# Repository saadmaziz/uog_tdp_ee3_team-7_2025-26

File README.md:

# UoG_TDP-EE3_Team_7
Design Files for the 3rd year EEE team design project at the University of Glasgow. Line following rover, with obstacle avoidance, traffic lights detection, remote control using an ESP-32 connected to a laptop and a Logitech 3D Pro Joystick.
The  Centeral processor is a Freescale NXP Frdm KL25Z.

1 - Team Organisation and 6 - General Documents are not uploaded as they may contain non-relavant information that should not be made public

The team consisted of 5 members.

My personal contributions spanned all of the software, all of the mechanical design, a substantial part of the electronic hardware design, and most of the integration.

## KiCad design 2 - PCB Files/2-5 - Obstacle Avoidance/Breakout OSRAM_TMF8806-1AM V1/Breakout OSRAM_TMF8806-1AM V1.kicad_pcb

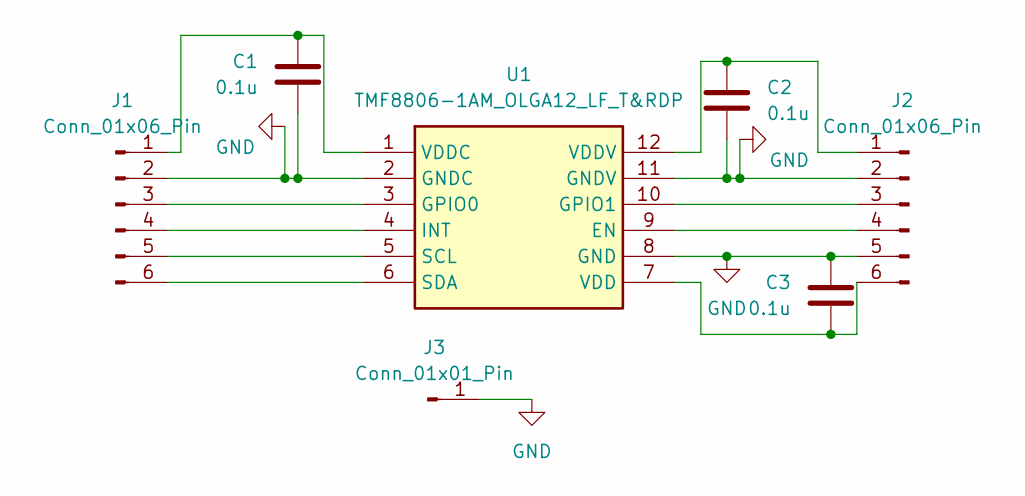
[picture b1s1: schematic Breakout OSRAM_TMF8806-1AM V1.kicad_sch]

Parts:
C1, C2, C3: 0.1u; C_0603_1608Metric
J1, J2: Conn_01x06_Pin; PinHeader_1x06_P2.54mm_Vertical
J3: Conn_01x01_Pin; PinHeader_1x01_P2.54mm_Vertical
U1: TMF8806-1AM_OLGA12_LF_T&RDP; TMF88061AMOLGA12LFTRDP; Manufacturer_Part_Number TMF8806-1AM OLGA12 LF T&RDP

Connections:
GND: C1.2, C2.2, C3.1, J1.2, J2.2, J2.5, J3.1, U1.2 (GNDC), U1.8 (GND), U1.11 (GNDV)
unnamed: C1.1, J1.1, U1.1 (VDDC)
unnamed: J1.3, U1.3 (GPIO0)
unnamed: J1.4, U1.4 (INT)
unnamed: J1.5, U1.5 (SCL)
unnamed: J1.6, U1.6 (SDA)
unnamed: C2.1, J2.1, U1.12 (VDDV)
unnamed: J2.3, U1.10 (GPIO1)
unnamed: J2.4, U1.9 (EN)
unnamed: C3.2, J2.6, U1.7 (VDD)

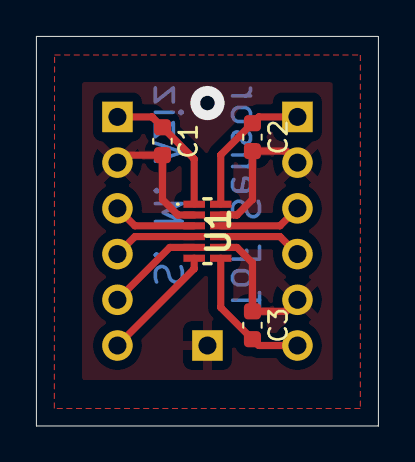
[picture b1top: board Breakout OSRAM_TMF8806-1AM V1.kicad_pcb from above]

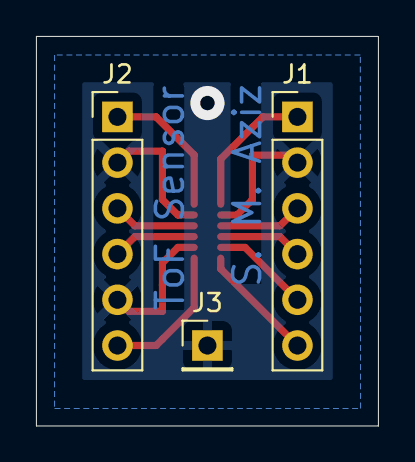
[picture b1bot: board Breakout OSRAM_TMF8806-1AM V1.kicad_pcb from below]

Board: 2 copper layers, 19.0 x 21.6 mm, 7 parts (3 on the bottom side), 10 nets.

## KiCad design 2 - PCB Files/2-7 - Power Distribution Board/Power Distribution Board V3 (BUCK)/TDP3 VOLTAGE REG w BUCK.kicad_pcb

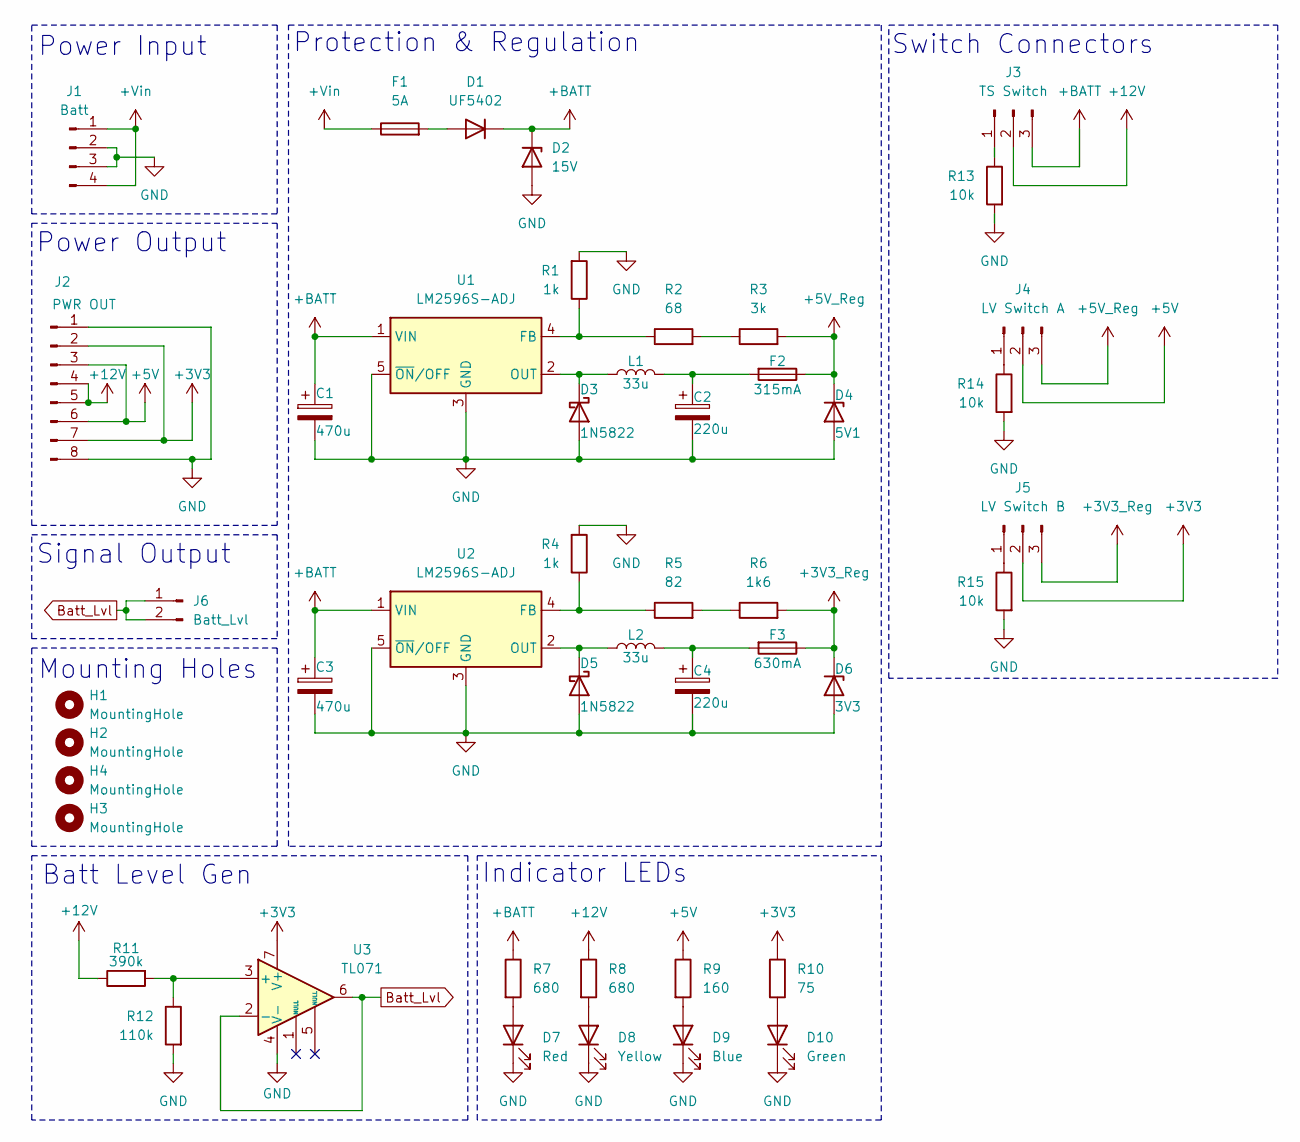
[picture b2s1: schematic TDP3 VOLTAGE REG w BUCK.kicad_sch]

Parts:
C1, C3: 470u; CP_Radial_D13.0mm_P5.00mm
C2, C4: 220u; CP_Radial_D10.0mm_P5.00mm
D1: UF5402; D_DO-201AD_P15.24mm_Horizontal
D2: 15V; D_DO-35_SOD27_P7.62mm_Horizontal
D3, D5: 1N5822; D_DO-201AD_P15.24mm_Horizontal
D4: 5V1; D_DO-35_SOD27_P7.62mm_Horizontal
D6: 3V3; D_DO-35_SOD27_P7.62mm_Horizontal
D7: Red; LED_0805_2012Metric_Pad1.15x1.40mm_HandSolder
D8: Yellow; LED_0805_2012Metric_Pad1.15x1.40mm_HandSolder
D9: Blue; LED_0805_2012Metric_Pad1.15x1.40mm_HandSolder
D10: Green; LED_0805_2012Metric_Pad1.15x1.40mm_HandSolder
F1: 5A; CamdenBoss CFH02_W Fuse Holder
F2: 315mA; CamdenBoss CFH02_W Fuse Holder
F3: 630mA; CamdenBoss CFH02_W Fuse Holder
H1, H2, H3, H4: MountingHole; MountingHole_3.2mm_M3
J1: Batt; Molex_KK-254_AE-6410-04A_1x04_P2.54mm_Vertical
J2: PWR OUT; PinHeader_1x08_P2.54mm_Vertical
J3: TS Switch; Molex_KK-254_AE-6410-03A_1x03_P2.54mm_Vertical
J4: LV Switch A; Molex_KK-254_AE-6410-03A_1x03_P2.54mm_Vertical
J5: LV Switch B; Molex_KK-254_AE-6410-03A_1x03_P2.54mm_Vertical
J6: Batt_Lvl; PinHeader_1x02_P2.54mm_Vertical
L1, L2: 33u; L_12x12mm_H6mm
R1, R4: 1k; R_0805_2012Metric_Pad1.20x1.40mm_HandSolder
R2: 68; R_0805_2012Metric_Pad1.20x1.40mm_HandSolder
R3: 3k; R_0805_2012Metric_Pad1.20x1.40mm_HandSolder
R5: 82; R_0805_2012Metric_Pad1.20x1.40mm_HandSolder
R6: 1k6; R_0805_2012Metric_Pad1.20x1.40mm_HandSolder
R7, R8: 680; R_0805_2012Metric_Pad1.20x1.40mm_HandSolder
R9: 160; R_0805_2012Metric_Pad1.20x1.40mm_HandSolder
R10: 75; R_0805_2012Metric_Pad1.20x1.40mm_HandSolder
R11: 390k; R_0805_2012Metric_Pad1.20x1.40mm_HandSolder
R12: 110k; R_0805_2012Metric_Pad1.20x1.40mm_HandSolder
R13, R14, R15: 10k; R_0805_2012Metric_Pad1.20x1.40mm_HandSolder
U1, U2: LM2596S-ADJ; TO-263-5_TabPin3
U3: TL071; DIP-8_W7.62mm_LongPads

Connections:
+3V3: J2.2, J2.7, J5.2, R10.1, U3.7 (V+)
+3V3_Reg: D6.1 (K), F3.1, J5.3, R6.2
+5V: J2.3, J2.6, J4.2, R9.1
+5V_Reg: D4.1 (K), F2.1, J4.3, R3.2
+12V: J2.4, J2.5, J3.2, R8.1, R11.1
+BATT: C1.1, C3.1, D1.1 (K), D2.1 (K), J3.3, R7.1, U1.1 (VIN), U2.1 (VIN)
+Vin: F1.1, J1.1, J1.4
Batt_Lvl: J6.1, J6.2, U3.2 (-), U3.6
GND: C1.2, C2.2, C3.2, C4.2, D2.2 (A), D3.2 (A), D4.2 (A), D5.2 (A), D6.2 (A), D7.1 (K), D8.1 (K), D9.1 (K), D10.1 (K), J1.2, J1.3, J2.1, J2.8, R1.2, R4.2, R12.2, R13.2, R14.2, R15.2, U1.3 (GND), U1.5 (~ON/OFF), U2.3 (GND), U2.5 (~ON/OFF), U3.4 (V-)
unnamed: C2.1, F2.2, L1.2
unnamed: C4.1, F3.2, L2.2
unnamed: D1.2 (A), F1.2
unnamed: D3.1 (K), L1.1, U1.2 (OUT)
unnamed: D5.1 (K), L2.1, U2.2 (OUT)
unnamed: D7.2 (A), R7.2
unnamed: D8.2 (A), R8.2
unnamed: D9.2 (A), R9.2
unnamed: D10.2 (A), R10.2
unnamed: J3.1, R13.1
unnamed: J4.1, R14.1
unnamed: J5.1, R15.1
unnamed: R2.2, R3.1
unnamed: R5.2, R6.1
unnamed: R1.1, R2.1, U1.4 (FB)
unnamed: R4.1, R5.1, U2.4 (FB)
unnamed: R11.2, R12.1, U3.3 (+)

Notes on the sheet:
Mounting Holes
Power Input
Indicator LEDs
Power Output
Signal Output
Switch Connectors
Batt Level Gen
Protection & Regulation

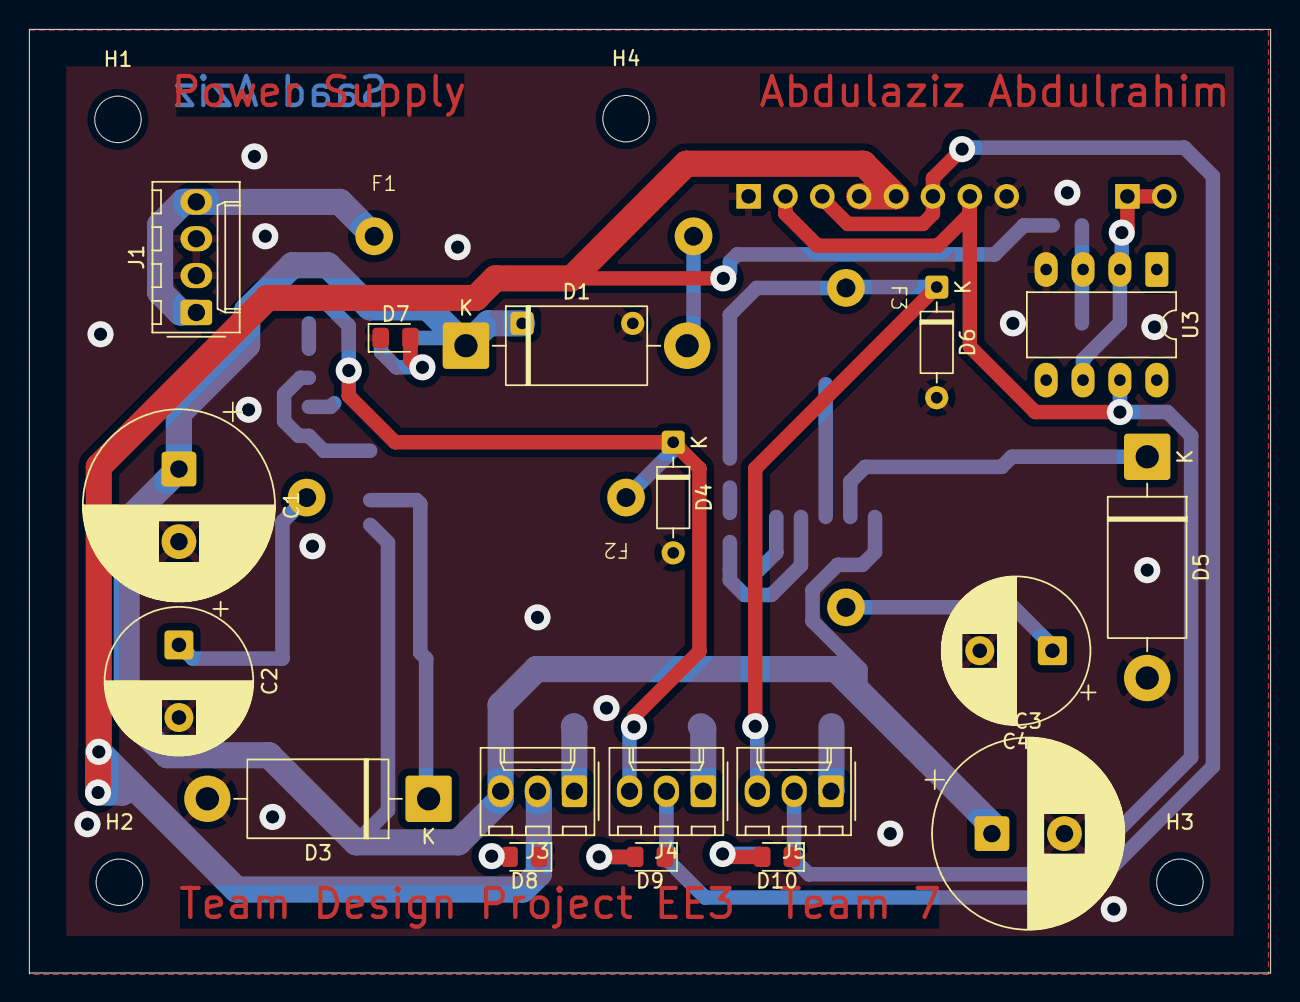
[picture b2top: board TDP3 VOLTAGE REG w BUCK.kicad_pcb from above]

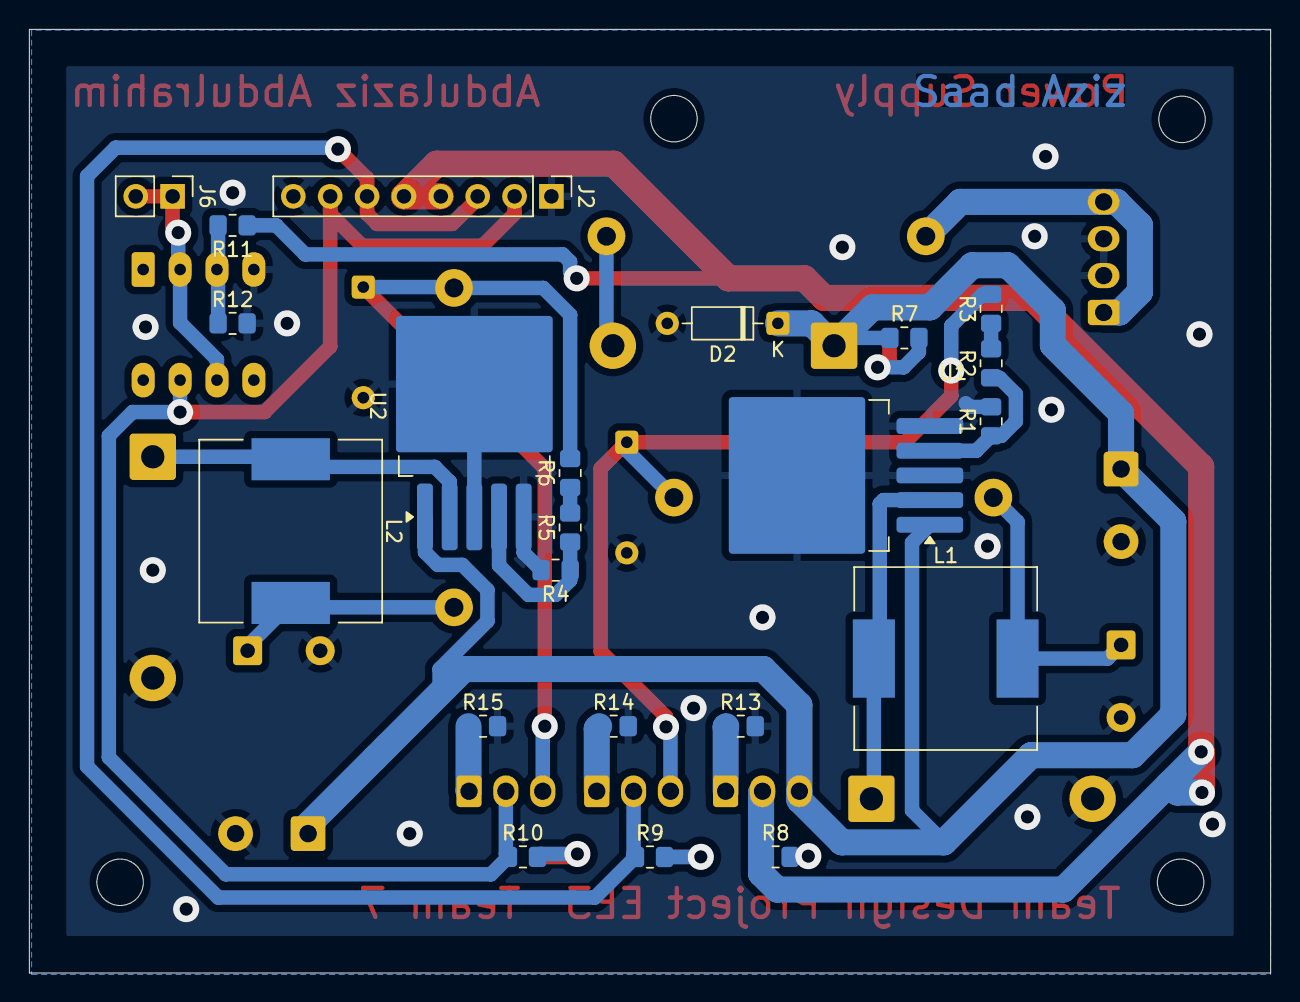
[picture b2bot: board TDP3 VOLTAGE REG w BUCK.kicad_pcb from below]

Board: 2 copper layers, 85.5 x 65.0 mm, 47 parts (22 on the bottom side), 26 nets.

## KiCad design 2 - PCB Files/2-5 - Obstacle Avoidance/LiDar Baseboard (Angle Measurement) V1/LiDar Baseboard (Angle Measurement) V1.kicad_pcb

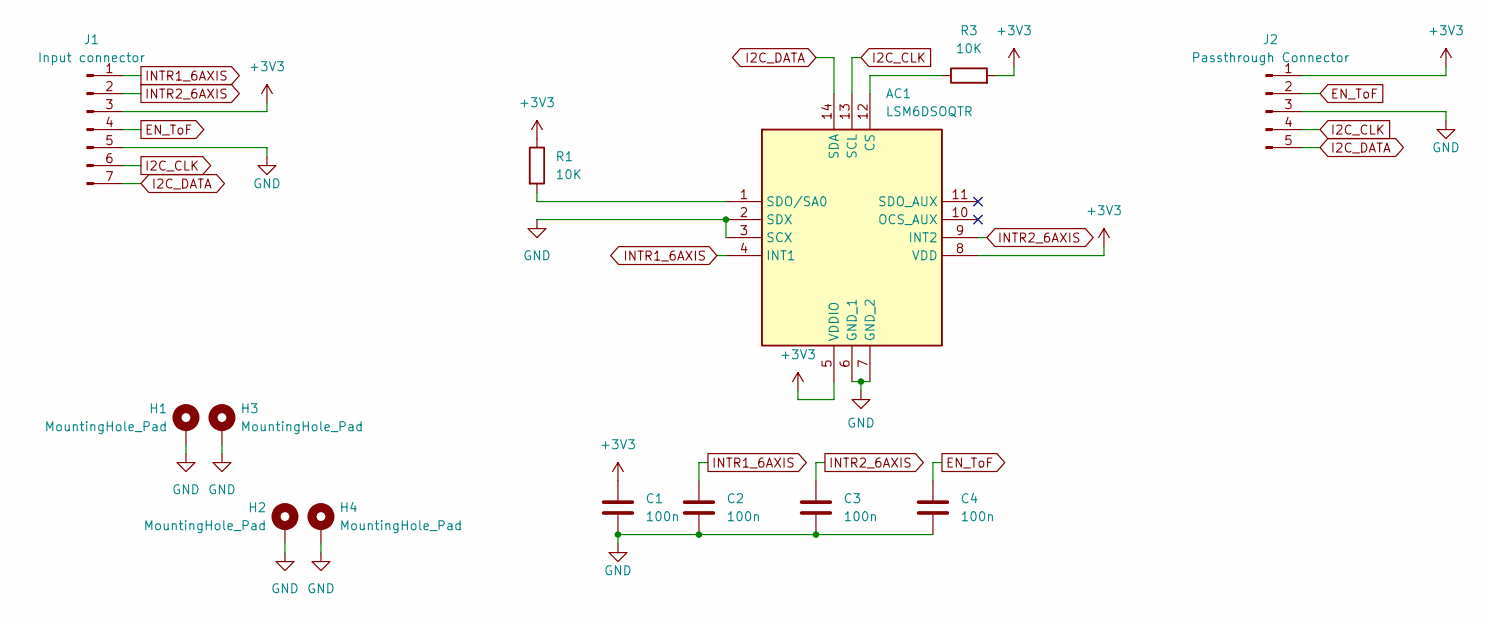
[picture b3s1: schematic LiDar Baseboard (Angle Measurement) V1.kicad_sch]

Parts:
AC1: LSM6DSOQTR; LSM6DSO_Breakout; Manufacturer_Part_Number LSM6DSOTR; Mouser Part Number 511-LSM6DSOTR
C1, C2, C3, C4: 100n; C_0805_2012Metric_Pad1.18x1.45mm_HandSolder
H1, H2, H3, H4: MountingHole_Pad; MountingHole_3.2mm_M3_DIN965_Pad_TopBottom
J1: Input connector; PinHeader_1x07_P2.54mm_Vertical
J2: Passthrough Connector; PinHeader_1x05_P2.54mm_Vertical
R1, R3: 10K; R_0805_2012Metric_Pad1.20x1.40mm_HandSolder

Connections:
+3V3: AC1.5 (VDDIO), AC1.8 (VDD), C1.1, J1.3, J2.1, R1.1, R3.2
EN_ToF: C4.1, J1.4, J2.2
GND: AC1.2 (SDX), AC1.3 (SCX), AC1.6 (GND_1), AC1.7 (GND_2), C1.2, C2.2, C3.2, C4.2, H1.1, H2.1, H3.1, H4.1, J1.5, J2.3; also elsewhere on the board
I2C_CLK: AC1.13 (SCL), J1.6, J2.4
I2C_DATA: AC1.14 (SDA), J1.7, J2.5
INTR1_6AXIS: AC1.4 (INT1), C2.1, J1.1
INTR2_6AXIS: AC1.9 (INT2), C3.1, J1.2
unnamed: AC1.12 (CS), R3.1
unnamed 8: AC1.1 (SDO/SA0), R1.2; also elsewhere on the board

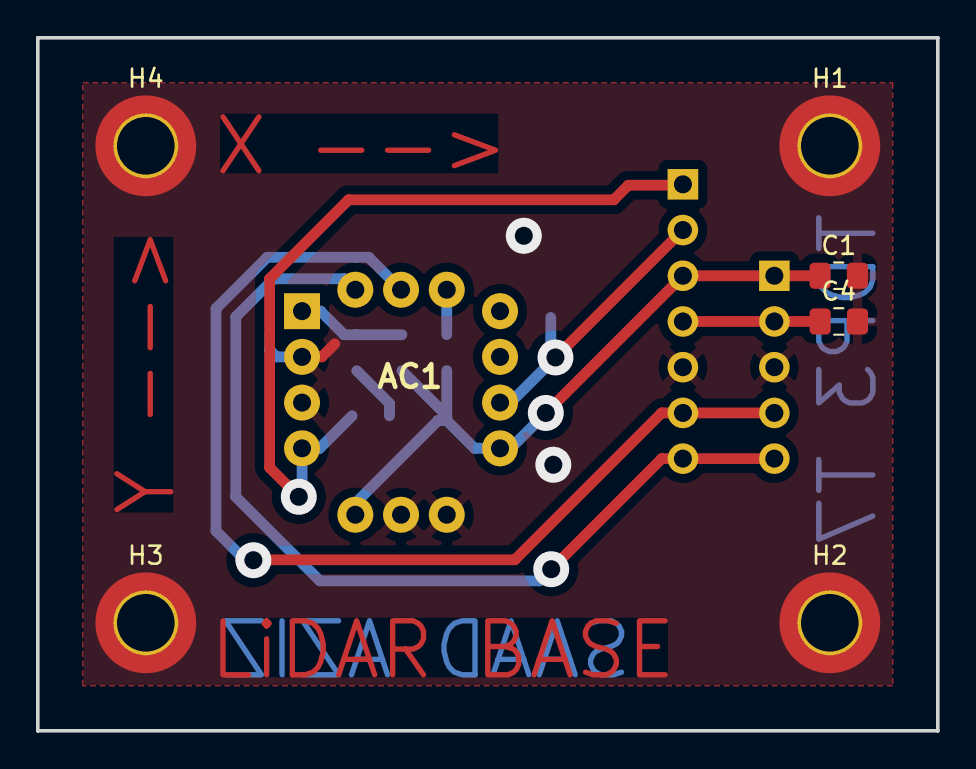
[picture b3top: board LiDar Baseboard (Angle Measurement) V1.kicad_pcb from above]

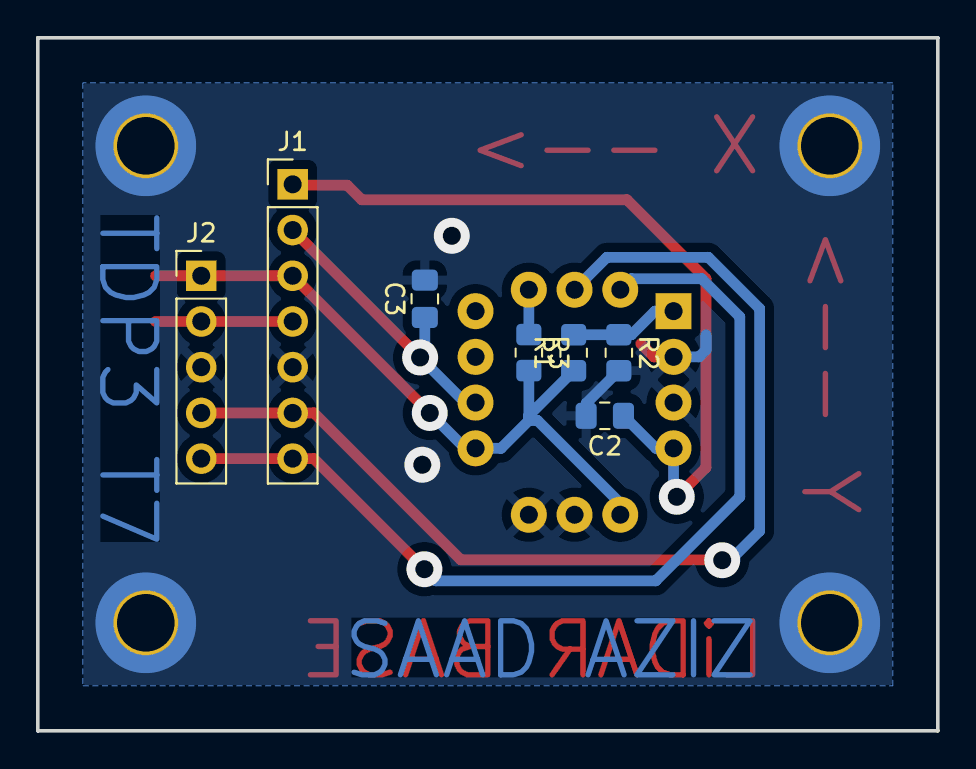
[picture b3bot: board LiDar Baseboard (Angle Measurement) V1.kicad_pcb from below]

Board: 2 copper layers, 50.0 x 38.5 mm, 14 parts (7 on the bottom side), 9 nets.

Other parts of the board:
R2: 10K; R_0805_2012Metric_Pad1.20x1.40mm_HandSolder

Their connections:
GND: R2.2; also elsewhere on the board
unnamed 8: R2.1; also elsewhere on the board

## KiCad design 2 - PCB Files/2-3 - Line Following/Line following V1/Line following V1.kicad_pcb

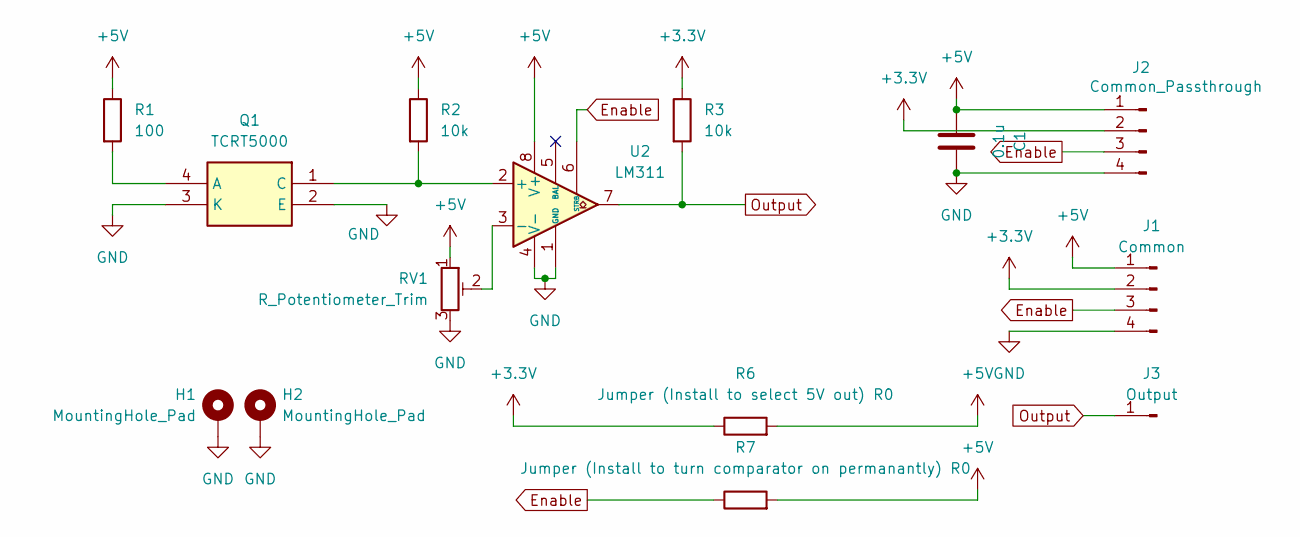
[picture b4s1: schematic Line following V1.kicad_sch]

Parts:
C1: 0.1u; C_0805_2012Metric_Pad1.18x1.45mm_HandSolder
H1, H2: MountingHole_Pad; MountingHole_5.3mm_M5_DIN965_Pad_TopBottom
J1: Common; PinHeader_1x04_P2.54mm_Vertical
J2: Common_Passthrough; PinHeader_1x04_P2.54mm_Vertical
J3: Output; PinHeader_1x01_P2.54mm_Vertical
Q1: TCRT5000; Manufacturer_Part_Number TCRT5000
R1: 100; R_0805_2012Metric_Pad1.20x1.40mm_HandSolder
R2, R3: 10k; R_0805_2012Metric_Pad1.20x1.40mm_HandSolder
R6: Jumper (Install to select 5V out) R0; R_0805_2012Metric_Pad1.20x1.40mm_HandSolder
R7: Jumper (Install to turn comparator on permanantly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; R_0805_2012Metric_Pad1.20x1.40mm_HandSolder
RV1: R_Potentiometer_Trim; Potentiometer_Bourns_3266W_Vertical
U2: LM311; DIP-8_W7.62mm_LongPads

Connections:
+3.3V: J1.2, J2.2, R3.1, R6.1
+5V: C1.2, J1.1, J2.1, R1.1, R2.1, R6.2, R7.2, RV1.1, U2.8 (V+)
Enable: J1.3, J2.3, R7.1, U2.6 (STRB)
GND: C1.1, H1.1, H2.1, J1.4, J2.4, Q1.2 (E), Q1.3 (K), RV1.3, U2.1 (GND), U2.4 (V-)
unnamed: Q1.4 (A), R1.2
unnamed: Q1.1 (C), R2.2, U2.2 (+)
unnamed: RV1.2, U2.3 (-)
Output: J3.1, R3.2, U2.7

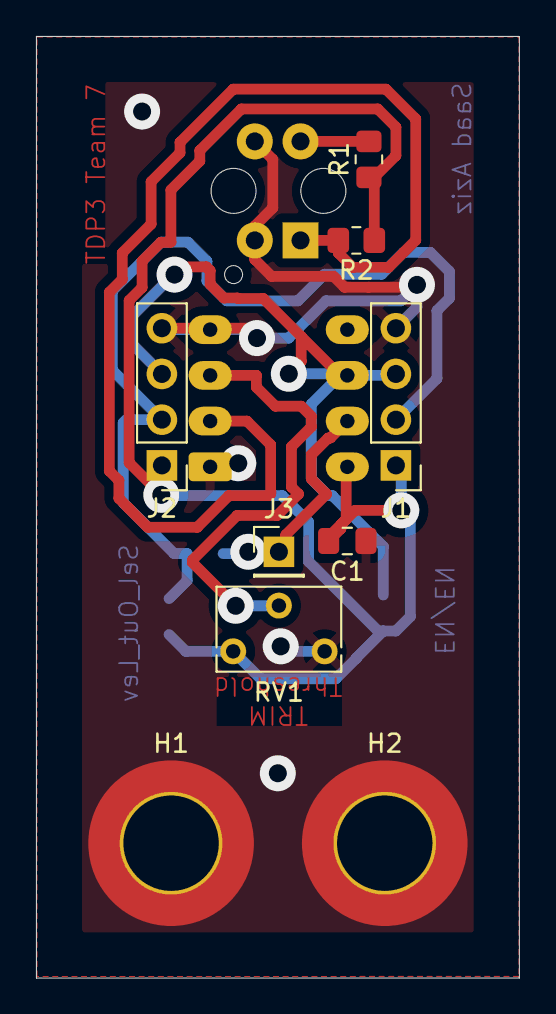
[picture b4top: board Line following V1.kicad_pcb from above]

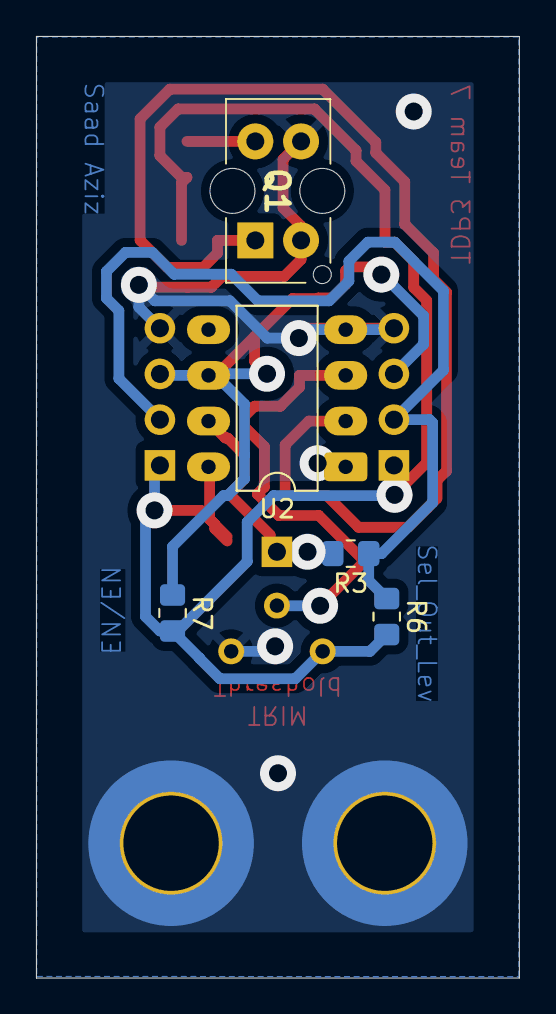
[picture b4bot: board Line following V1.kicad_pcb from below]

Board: 2 copper layers, 26.8 x 52.3 mm, 14 parts (5 on the bottom side), 8 nets.

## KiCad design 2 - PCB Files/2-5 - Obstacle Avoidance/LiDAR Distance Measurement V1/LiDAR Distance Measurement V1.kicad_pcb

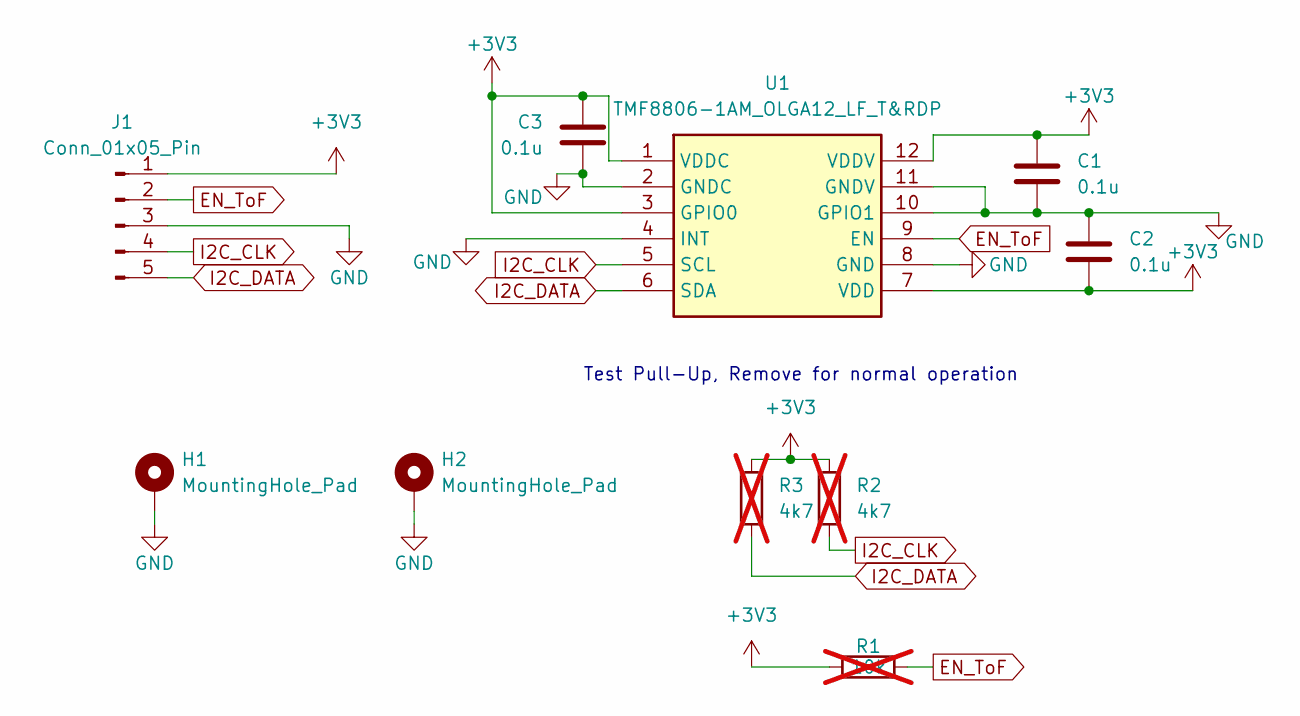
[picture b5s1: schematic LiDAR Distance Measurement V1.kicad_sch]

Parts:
C1, C2, C3: 0.1u; C_0603_1608Metric
H1, H2: MountingHole_Pad; MountingHole_3.2mm_M3_DIN965_Pad_TopBottom
J1: Conn_01x05_Pin; PinHeader_1x05_P2.54mm_Vertical
R1: 10k; R_0805_2012Metric_Pad1.20x1.40mm_HandSolder; not fitted
R2, R3: 4k7; R_0805_2012Metric_Pad1.20x1.40mm_HandSolder; not fitted
U1: TMF8806-1AM_OLGA12_LF_T&RDP; TMF88061AMOLGA12LFTRDP; Manufacturer_Part_Number TMF8806-1AM OLGA12 LF T&RDP

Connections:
+3V3: C1.1, C2.2, C3.1, J1.1, R1.1, R2.1, R3.1, U1.1 (VDDC), U1.3 (GPIO0), U1.7 (VDD), U1.12 (VDDV)
EN_ToF: J1.2, R1.2, U1.9 (EN)
GND: C1.2, C2.1, C3.2, H1.1, H2.1, J1.3, U1.2 (GNDC), U1.4 (INT), U1.8 (GND), U1.10 (GPIO1), U1.11 (GNDV)
I2C_CLK: J1.4, R2.2, U1.5 (SCL)
I2C_DATA: J1.5, R3.2, U1.6 (SDA)

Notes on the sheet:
Test Pull-Up, Remove for normal operation

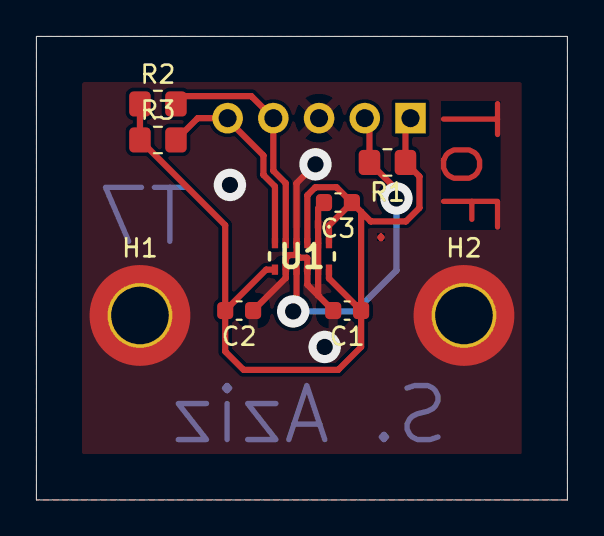
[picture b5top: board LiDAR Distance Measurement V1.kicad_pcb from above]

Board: 2 copper layers, 29.5 x 25.8 mm, 10 parts (1 on the bottom side), 5 nets.

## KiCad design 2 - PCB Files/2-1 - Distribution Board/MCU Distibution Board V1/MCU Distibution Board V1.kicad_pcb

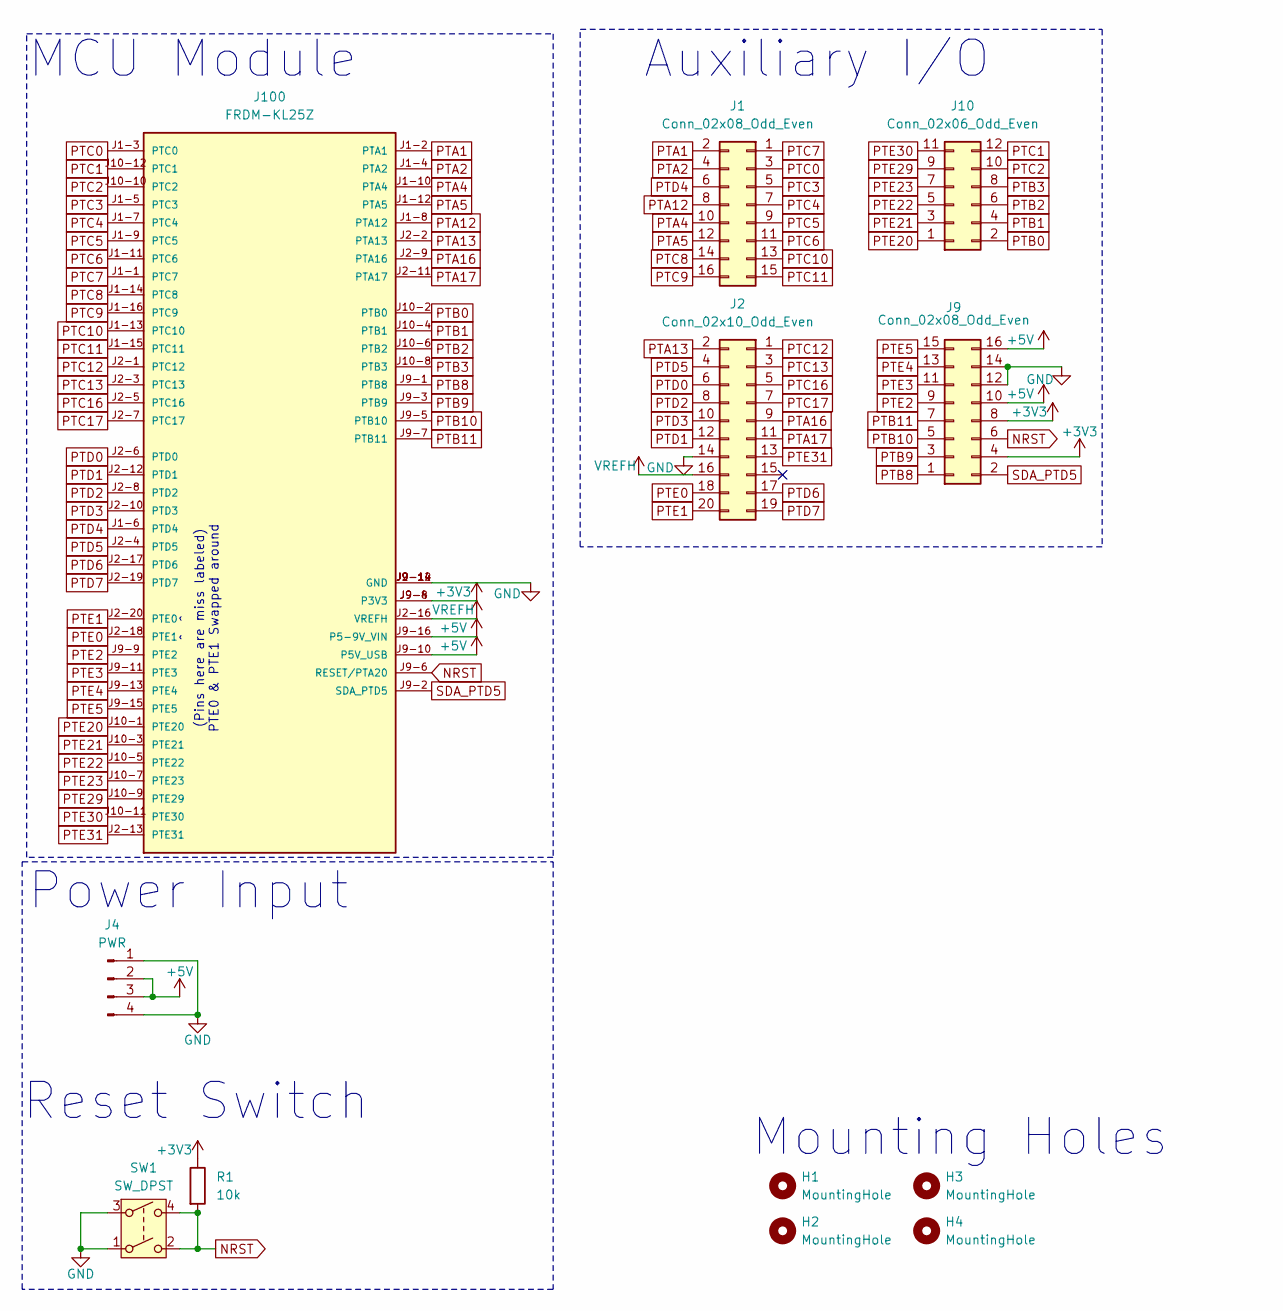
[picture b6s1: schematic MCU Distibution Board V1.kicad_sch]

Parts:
H1, H2, H3, H4: MountingHole; MountingHole_3.2mm_M3
J1, J9: Conn_02x08_Odd_Even; PinSocket_2x08_P2.54mm_Vertical
J2: Conn_02x10_Odd_Even; PinSocket_2x10_P2.54mm_Vertical
J4: PWR; Molex_KK-254_AE-6410-04A_1x04_P2.54mm_Vertical
J10: Conn_02x06_Odd_Even; PinSocket_2x06_P2.54mm_Vertical
J100: FRDM-KL25Z
R1: 10k; R_0805_2012Metric_Pad1.20x1.40mm_HandSolder
SW1: SW_DPST; SW_Push_2P1T_Toggle_CK_PVA1xxH1xxxxxxV2

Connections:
+3V3: J9.4, J9.8, J100.J9-4 (P3V3), J100.J9-8 (P3V3), R1.1
+5V: J4.2, J4.3, J9.10, J9.16, J100.J9-10 (P5V_USB), J100.J9-16 (P5-9V_VIN)
GND: J2.14, J4.1, J4.4, J9.12, J9.14, J100.J2-14 (GND), J100.J9-12 (GND), J100.J9-14 (GND), SW1.1, SW1.3
NRST: J9.6, J100.J9-6 (RESET/PTA20), R1.2, SW1.2, SW1.4
PTA1: J1.2, J100.J1-2 (PTA1)
PTA2: J1.4, J100.J1-4 (PTA2)
PTA4: J1.10, J100.J1-10 (PTA4)
PTA5: J1.12, J100.J1-12 (PTA5)
PTA12: J1.8, J100.J1-8 (PTA12)
PTA13: J2.2, J100.J2-2 (PTA13)
PTA16: J2.9, J100.J2-9 (PTA16)
PTA17: J2.11, J100.J2-11 (PTA17)
PTB0: J10.2, J100.J10-2 (PTB0)
PTB1: J10.4, J100.J10-4 (PTB1)
PTB2: J10.6, J100.J10-6 (PTB2)
PTB3: J10.8, J100.J10-8 (PTB3)
PTB8: J9.1, J100.J9-1 (PTB8)
PTB9: J9.3, J100.J9-3 (PTB9)
PTB10: J9.5, J100.J9-5 (PTB10)
PTB11: J9.7, J100.J9-7 (PTB11)
PTC0: J1.3, J100.J1-3 (PTC0)
PTC1: J10.12, J100.J10-12 (PTC1)
PTC2: J10.10, J100.J10-10 (PTC2)
PTC3: J1.5, J100.J1-5 (PTC3)
PTC4: J1.7, J100.J1-7 (PTC4)
PTC5: J1.9, J100.J1-9 (PTC5)
PTC6: J1.11, J100.J1-11 (PTC6)
PTC7: J1.1, J100.J1-1 (PTC7)
PTC8: J1.14, J100.J1-14 (PTC8)
PTC9: J1.16, J100.J1-16 (PTC9)
PTC10: J1.13, J100.J1-13 (PTC10)
PTC11: J1.15, J100.J1-15 (PTC11)
PTC12: J2.1, J100.J2-1 (PTC12)
PTC13: J2.3, J100.J2-3 (PTC13)
PTC16: J2.5, J100.J2-5 (PTC16)
PTC17: J2.7, J100.J2-7 (PTC17)
PTD0: J2.6, J100.J2-6 (PTD0)
PTD1: J2.12, J100.J2-12 (PTD1)
PTD2: J2.8, J100.J2-8 (PTD2)
PTD3: J2.10, J100.J2-10 (PTD3)
PTD4: J1.6, J100.J1-6 (PTD4)
PTD5: J2.4, J100.J2-4 (PTD5)
PTD6: J2.17, J100.J2-17 (PTD6)
PTD7: J2.19, J100.J2-19 (PTD7)
PTE0: J2.18, J100.J2-18 (PTE1)
PTE1: J2.20, J100.J2-20 (PTE0)
PTE2: J9.9, J100.J9-9 (PTE2)
PTE3: J9.11, J100.J9-11 (PTE3)
PTE4: J9.13, J100.J9-13 (PTE4)
PTE5: J9.15, J100.J9-15 (PTE5)
PTE20: J10.1, J100.J10-1 (PTE20)
PTE21: J10.3, J100.J10-3 (PTE21)
PTE22: J10.5, J100.J10-5 (PTE22)
PTE23: J10.7, J100.J10-7 (PTE23)
PTE29: J10.9, J100.J10-9 (PTE29)
PTE30: J10.11, J100.J10-11 (PTE30)
PTE31: J2.13, J100.J2-13 (PTE31)
SDA_PTD5: J9.2, J100.J9-2 (SDA_PTD5)
VREFH: J2.16, J100.J2-16 (VREFH)

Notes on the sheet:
Mounting Holes
Power Input
Auxiliary I/O
Reset Switch
MCU Module
^ ^ (Pins here are miss labeled) PTE0 & PTE1 Swapped around

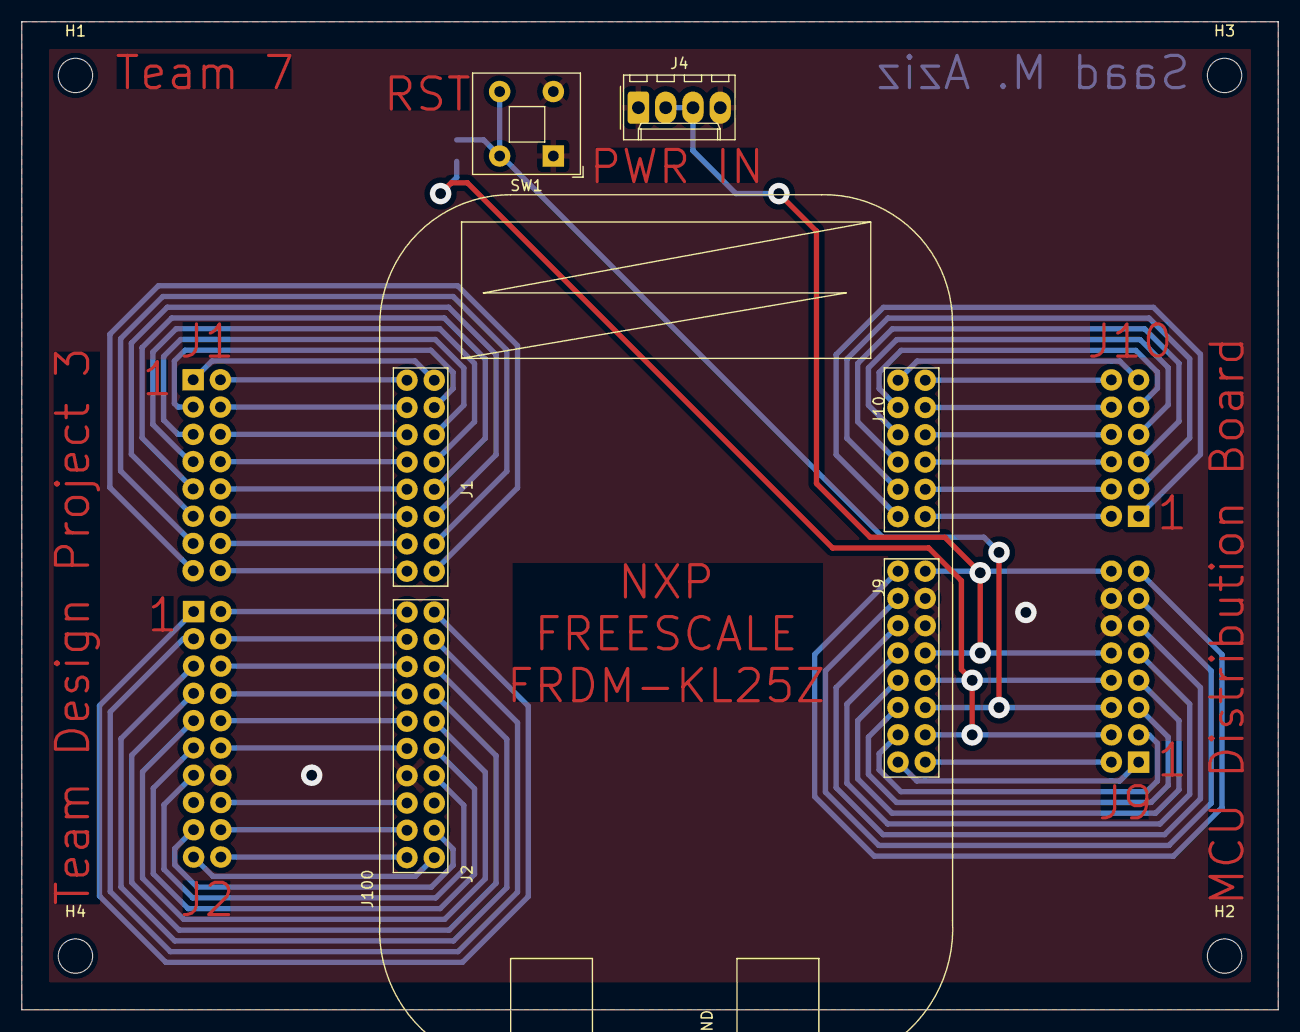
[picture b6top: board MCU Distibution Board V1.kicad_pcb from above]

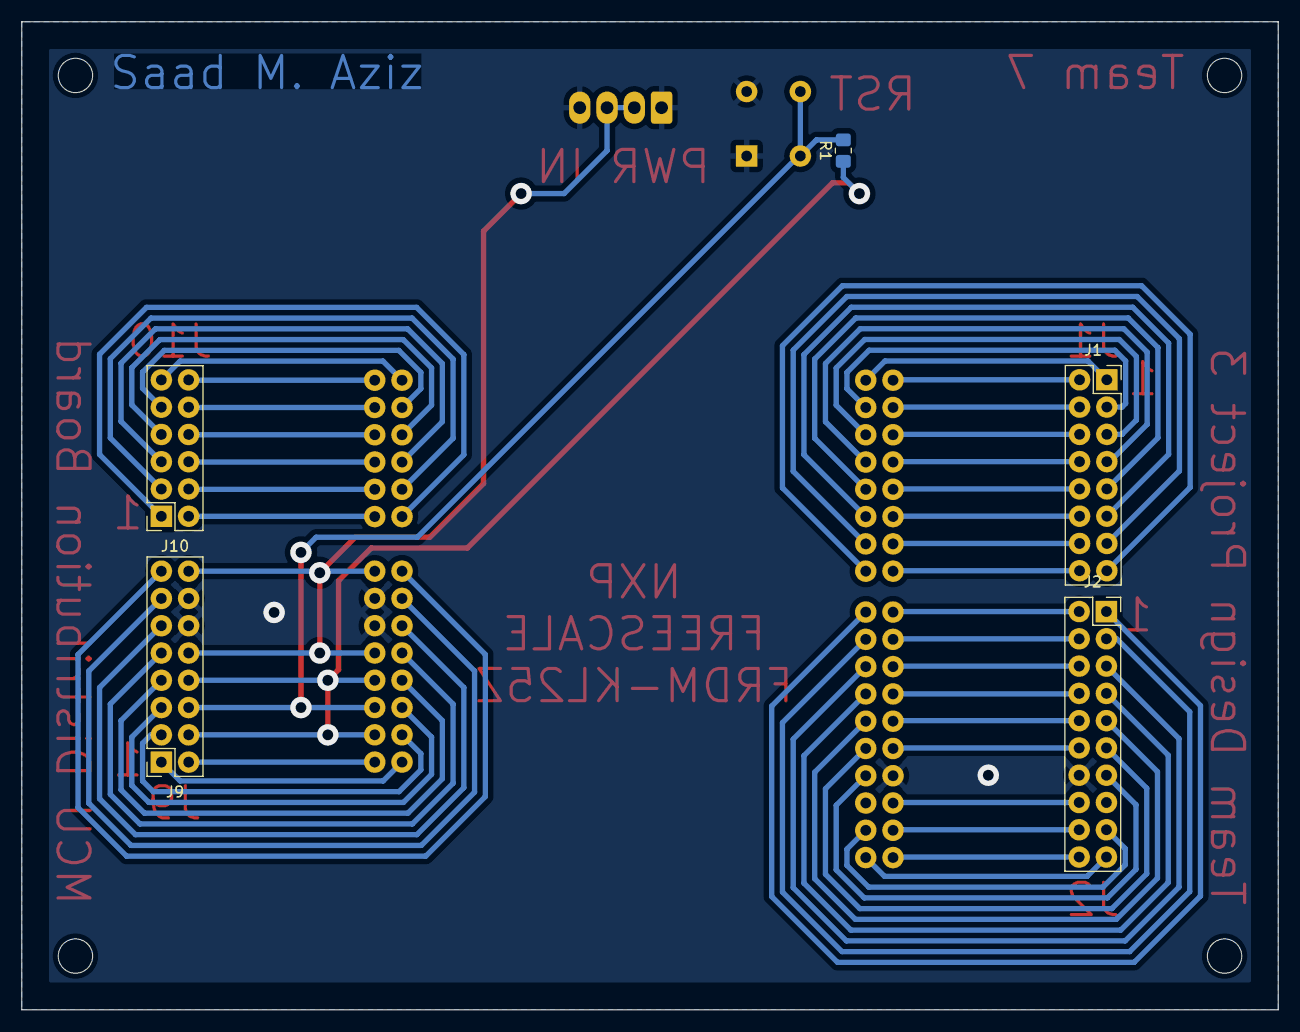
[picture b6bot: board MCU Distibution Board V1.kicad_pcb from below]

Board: 2 copper layers, 117.0 x 92.0 mm, 12 parts (5 on the bottom side), 59 nets.
